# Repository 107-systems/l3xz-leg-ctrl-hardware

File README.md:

`l3xz-leg-ctrl-hardware`
========================

Custom leg controller board for the [L3X-Z Hexapod](https://github.com/107-systems/l3xz-hw).

<p align="center">
  
</p>

## Firmware
[l3xz-leg-ctrl-firmware](https://github.com/107-systems/l3xz-leg-ctrl-firmware)

## Pin Usage
### Arduino Nano 33 IoT connector CN1
| **Pin** | **Pin Name** | **Signal**    | **Description**                  |
|:-------:|:------------:|:-------------:|:--------------------------------:|
| 1       | D13/SCK      | SPI_SCK       | SPI for CAN and AS5048 encoder   |
| 2       | +3V3         | 3V3-rail      | supply voltage for board         |
| 3       | AREF         |               |                                  |
| 4       | DAC0/A0      |               |                                  |
| 5       | A1           | +BATT_MEAS    | measurement of input voltage     |
| 6       | A2           |               |                                  |
| 7       | A3           |               |                                  |
| 8       | A4/SDA       | I2C_SDA       | I2C for eeprom and qwiic         |
| 9       | A5/SCL       | I2C_SCL       | I2C for eeprom and qwiic         |
| 10      | A6           | LED3          | status LED 3                     |
| 11      | A7           | LED2          | status LED 2                     |
| 12      | VUSB/+5V0    |               |                                  |
| 13      | REC/RESET    | RESET         | Reset                            |
| 14      | GND          | GND           | GND                              |
| 15      | VIN          | power input   | power input for board            |
| 16      | D1/TX        | SERIAL_TX     | to connector CN3                 |
| 17      | D0/RX        | SERIAL_RX     | to connector CN3                 |
| 18      | RESET        | RESET         | Reset                            |
| 19      | GND          | GND           | GND                              |
| 20      | D2           | LED1          | status LED 1                     |
| 21      | D3           | MCP2515_CS    | chip select for CAN              |
| 22      | D4           | AS5048_1_CS   | chip select for AS5048 1         |
| 23      | D5           | AS5048_2_CS   | chip select for AS5048 2         |
| 24      | D6           | BUMPER        | input for bumper                 |
| 25      | D7           | SERVO1        | PWM output for servo 1           |
| 26      | D8           |               |                                  |
| 27      | D9           | MCP2515_INT   | CAN interrupt                    |
| 28      | D10          | SERVO2        | PWM output for servo 2           |
| 29      | D11/MOSI     | SPI_MOSI      | SPI for CAN and AS5048 encoder   |
| 30      | D12/MISO     | SPI_MISO      | SPI for CAN and AS5048 encoder   |

### Qwiic I2C connector CN2
JST SH 1mm 4-pin.

| **Pin** | **Signal**    |
|:-------:|:-------------:|
| 1       | GND           |
| 2       | VCC           |
| 3       | I2C_SDA       |
| 4       | I2C_SCL       |

### Serial connector CN3
JST SH 1mm 4-pin.

| **Pin** | **Signal**    |
|:-------:|:-------------:|
| 1       | GND           |
| 2       | VCC           |
| 3       | SERIAL_TX     |
| 4       | SERIAL_RX     |

### Dronecode CAN connector CN4 and CN5
JST GH 1.25mm 4-pin.

| **Pin** | **Signal**    |
|:-------:|:-------------:|
| 1       | CANVCC        |
| 2       | CANH          |
| 3       | CANL          |
| 4       | GND           |

### Power Input CN6
Würth WR-TBL 3.81mm 2-pin.

| **Pin** | **Signal**    |       **Description**        |
|:-------:|:-------------:|:----------------------------:|
| 1       | V-IN          | Directly to Arduino Nano VIN |
| 2       | GND           |                              |

Attention: V_IN is 5 to 21 V and is directly connected to VIN of the Arduino with a diode for reverse polarity protection.
It is also directly connected to +5V of the servo connector. So it should be limited to +6V if servos are used.

### Cervo connector CN7
2x3 pin-header 2.54 mm.

| **Pin** | **Signal**    | **Description**                  |
|:-------:|:-------------:|:--------------------------------:|
| 1+2     | servo-pwm     | 50 Hz pulse signal               |
| 3+4     | +5V           | directly connected to VIN        |
| 5+6     | GND           |                                  |

### Bumper Connector CN8
WAGO 733-362 2.5mm 2-pin.

| **Pin** | **Signal**    | **Description**                  |
|:-------:|:-------------:|:--------------------------------:|
| 1       | BUMPER        | 10k pull up to +3.3V             |
| 2       | GND           |                                  |

## BOM

| **Designator** | **Part Name**             | **Link**                  |
|:--------------:|:-------------------------:|:--------------------------------:|
| C1, C2, C3, C4, C5, C6, C9 | Capacitor 0603 100nF 25V  |           |
| C7, C8         | do not install            |           |
| C10, C11       | do not install            |           |
| CN1            | Arduino Nano              | https://www.reichelt.de/praez-buchsenleisten-2-54-mm-1x15-gerade-mpe-115-1-015-p187279.html |
| CN2, CN3       | JST SH SM04B-SRSS-TB      |                                  |
| CN4, CN5       | JST GH SM04B-GHS-TB       | https://www.voelkner.de/products/1102742/JST-Stiftgehaeuse-Platine-GH-Polzahl-Gesamt-4-Rastermass-1.25mm-SM04B-GHS-TB-LF-SN.html           |
| CN6            | Würth WR-TBL 691322310002 |                                  |
| CN7            | Pinheader 2.54 mm 2x3     | https://www.reichelt.de/stiftleisten-2-54-mm-2x03-gewinkelt-mpe-088-2-006-p119904.html      |
| CN8            | WAGO 733-362              | https://www.reichelt.de/print-stiftleiste-micro-rm-2-5-gewinkelt-2-pol--wago-733-362-p45863.html |
| D1             | LED 0603 green            | https://www.reichelt.de/led-smd-1608-0603-gruen-112-mcd-120--led-el-0603-gr1-p156254.html   |
| D2, D3         | MBR0530T1G                | https://www.reichelt.de/schottkydiode-30-v-0-5-a-sod-123-mbr0530t1g-ons-p219621.html        |
| D4             | LED 0603 yellow           | https://www.reichelt.de/led-smd-1608-0603-gelb-180-mcd-120--led-el-0603-ge-p156259.html     |
| D5             | LED 0603 red              | https://www.reichelt.de/led-smd-1608-0603-rot-180-mcd-120--led-el-0603-rt-p156256.html      |
| R1, R2, R3, R4, R6, R7, R8, R9, R10, R14 | Resistor 0603 10k         |           |
| R5, R15, R16   | Resistor 0603 3k3         |           |
| R11, 12        | do not install            |           |
| R13            | Resistor 0603 100k        |           |
| U1, U2         | AS5048A                   |           |
| U3             | 24LC64-I/SN               | https://www.reichelt.de/eeprom-seriell-64-kb-8-k-x-8-i2c-2-5--5-5-v-so-8-24lc64-i-sn-p40079.html |
| U4             | MCP2515-I/P DIP-18        | https://www.reichelt.de/can-controller-mit-spi-schnittstelle-dil-18-mcp-2515-i-p-p54514.html |
| U8 alternative | MCP2515-I/SO SO-18        | https://www.reichelt.de/can-controller-mit-spi-schnittstelle-2-7--5-5-v-so-18-mcp-2515-i-so-p54515.html |
| U9             | SN65HVD232D               |           |
| U9 alternative | SN65HVD230D               | https://www.reichelt.de/high-speed-can-transceiver-1-mbit-s-3-3-v-so-8-sn-65hvd230d-p58427.html |
| Y1             | Quartz 16 MHz 5x2.5mm     | https://www.reichelt.de/keramik-smd-quarz-3x5x1mm-16-0mhz-16-000000-mj-p85005.html          |

## PCB
### Top
<p align="center">
  </a>
</p>
### Bottom
<p align="center">
  </a>
</p>

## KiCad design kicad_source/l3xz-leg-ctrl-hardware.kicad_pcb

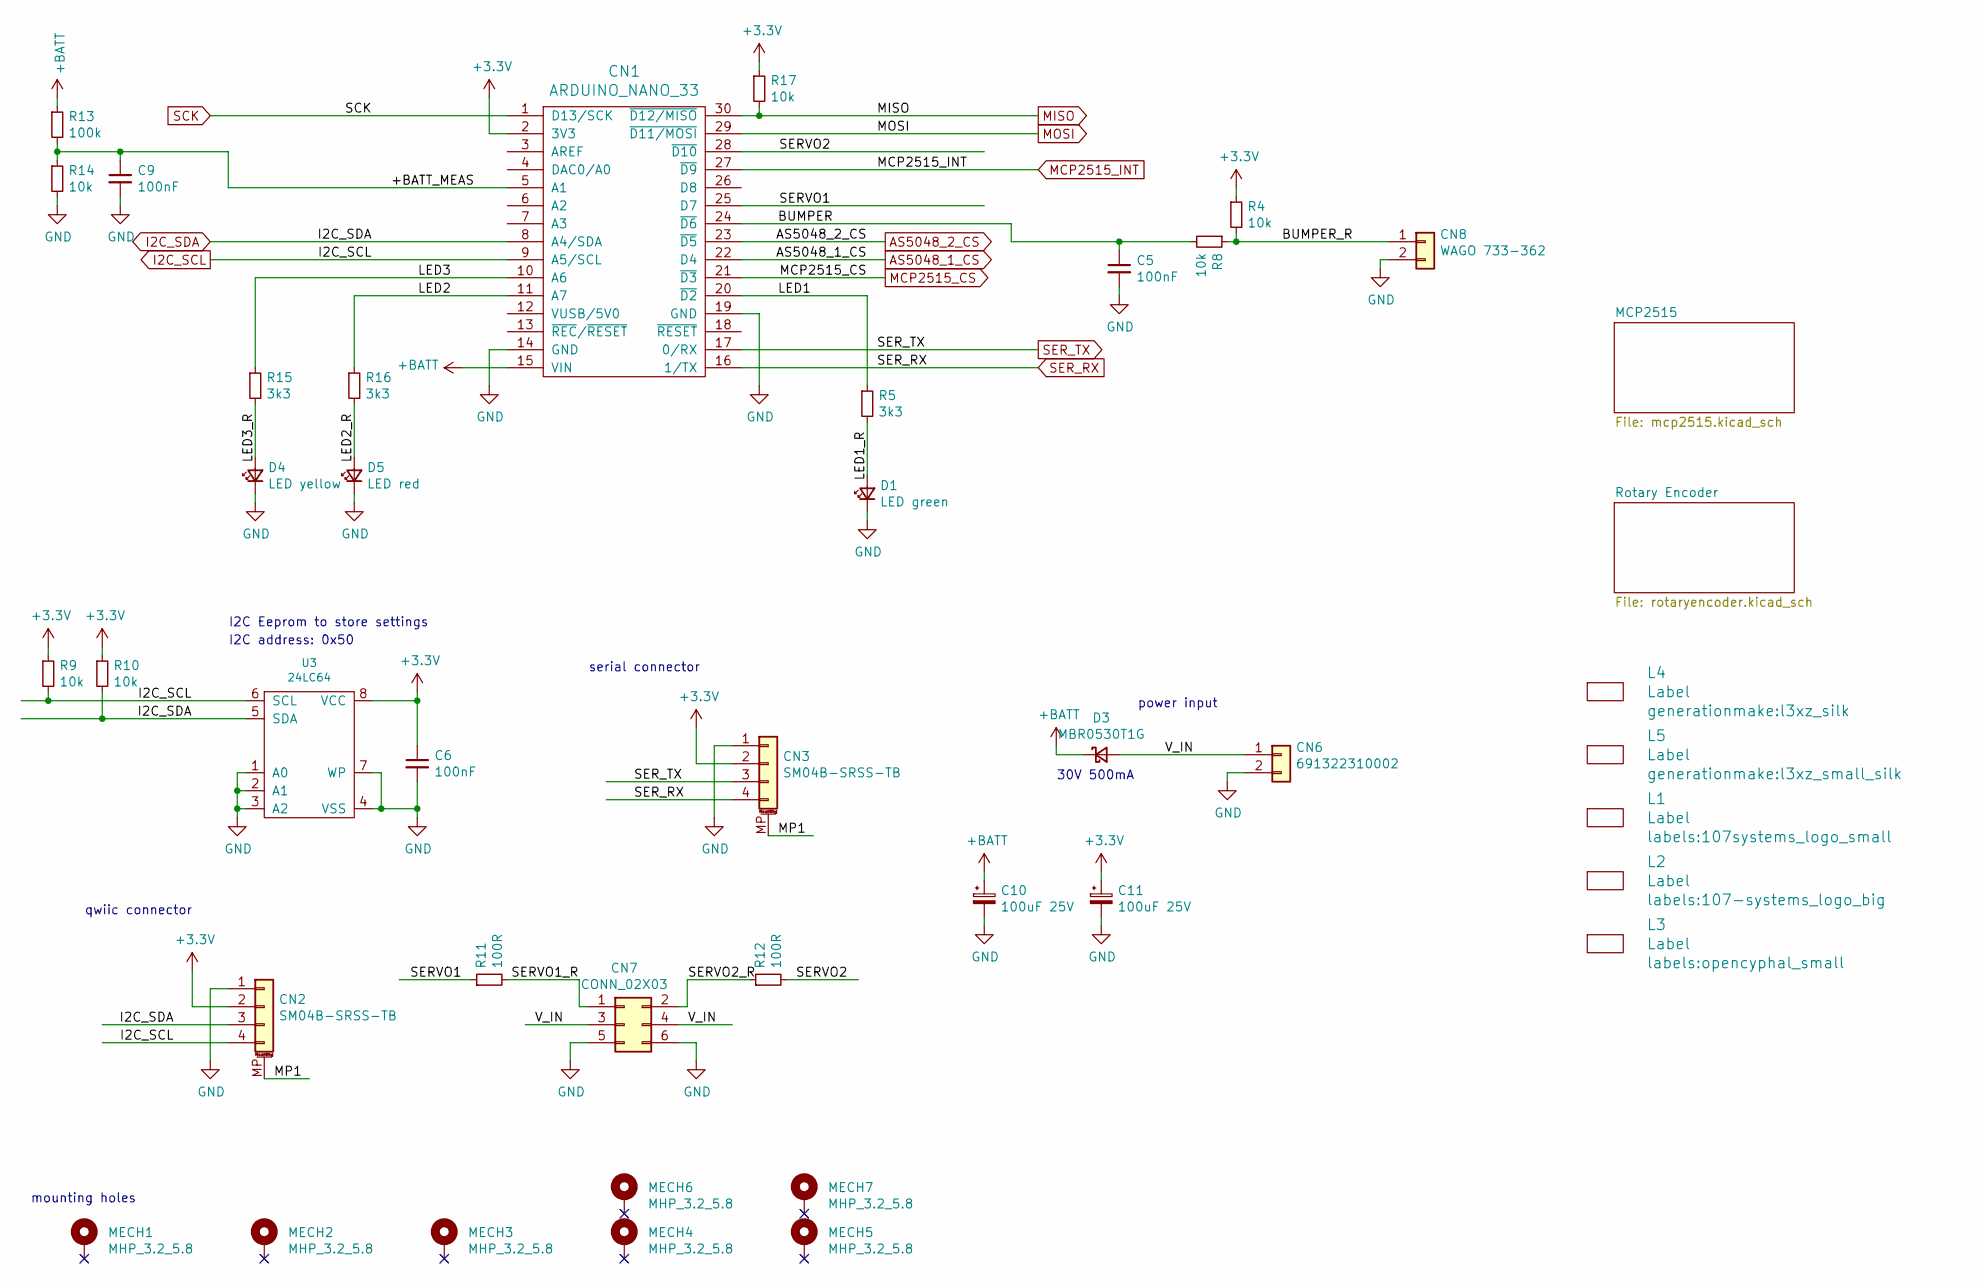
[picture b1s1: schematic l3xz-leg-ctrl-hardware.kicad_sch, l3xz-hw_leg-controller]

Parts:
C5, C6, C9: 100nF; C_0603_1608Metric
C10, C11: 100uF 25V; CP_Elec_8x10
CN1: ARDUINO_NANO_33
CN2, CN3: SM04B-SRSS-TB; JST_SH_SM04B-SRSS-TB_1x04-1MP_P1.00mm_Horizontal
CN6: 691322310002; WR-TBL_691322310002
CN7: CONN_02X03; PinHeader_2x03_P2.54mm_Horizontal
CN8: WAGO 733-362; WR-TBL_691382010002
D1: LED green; LED_0603
D3: MBR0530T1G; D_SOD-123
D4: LED yellow; LED_0603
D5: LED red; LED_0603
L1: Label; 107systems_logo_small
L2: Label; 107-systems_logo_big
L3: Label; opencyphal_small
L4: Label; l3xz_silk
L5: Label; l3xz_small_silk
MECH1, MECH2, MECH3, MECH4, MECH5, MECH6, MECH7: MHP_3.2_5.8
R4, R8, R9, R10, R14, R17: 10k; R_0603_1608Metric
R5, R15, R16: 3k3; R_0603_1608Metric
R11, R12: 100R; R_0603_1608Metric
R13: 100k; R_0603_1608Metric
U3: 24LC64; SOIC-8_3.9x4.9mm_P1.27mm

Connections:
+3.3V: C6.1, C11.1, CN1.2 (3V3), CN2.2, CN3.2, R4.1, R9.1, R10.1, R17.1, U3.8 (VCC); also elsewhere on the board
+BATT: C10.1, CN1.15 (VIN), D3.1 (K), R13.1; also elsewhere on the board
/+BATT_MEAS: C9.1, CN1.5 (A1), R13.2, R14.1
/BUMPER: C5.1, CN1.24 (~D6), R8.2
/BUMPER_R: CN8.1, R4.2, R8.1
/LED1: CN1.20 (~D2), R5.1
/LED1_R: D1.2 (A), R5.2
/LED2: CN1.11 (A7), R16.1
/LED2_R: D5.2 (A), R16.2
/LED3: CN1.10 (A6), R15.1
/LED3_R: D4.2 (A), R15.2
/MP1: CN2.MP (MountPin), CN3.MP (MountPin)
/SERVO1: CN1.25 (D7), R11.1
/SERVO1_R: CN7.1, R11.2
/SERVO2: CN1.28 (~D10), R12.2
/SERVO2_R: CN7.2, R12.1
/V_IN: CN6.1, CN7.3, CN7.4, D3.2 (A)
AS5048_1_CS: CN1.22 (D4); also elsewhere on the board
AS5048_2_CS: CN1.23 (~D5); also elsewhere on the board
GND: C5.2, C6.2, C9.2, C10.2, C11.2, CN1.14 (GND), CN1.19 (GND), CN2.1, CN3.1, CN6.2, CN7.5, CN7.6, CN8.2, D1.1 (K), D4.1 (K), D5.1 (K), R14.2, U3.1 (A0), U3.2 (A1), U3.3 (A2), U3.4 (VSS), U3.7 (WP); also elsewhere on the board
I2C_SCL: CN1.9 (A5/SCL), CN2.4, R9.2, U3.6 (SCL)
I2C_SDA: CN1.8 (A4/SDA), CN2.3, R10.2, U3.5 (SDA)
MCP2515_CS: CN1.21 (~D3); also elsewhere on the board
MCP2515_INT: CN1.27 (~D9); also elsewhere on the board
MISO: CN1.30 (~D12/MISO), R17.2; also elsewhere on the board
MOSI: CN1.29 (~D11/MOSI); also elsewhere on the board
SCK: CN1.1 (D13/SCK); also elsewhere on the board
SER_RX: CN1.16 (1/TX), CN3.4
SER_TX: CN1.17 (0/RX), CN3.3

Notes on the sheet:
serial connector
power input
I2C address: 0x50
qwiic connector
mounting holes
30V 500mA
I2C Eeprom to store settings

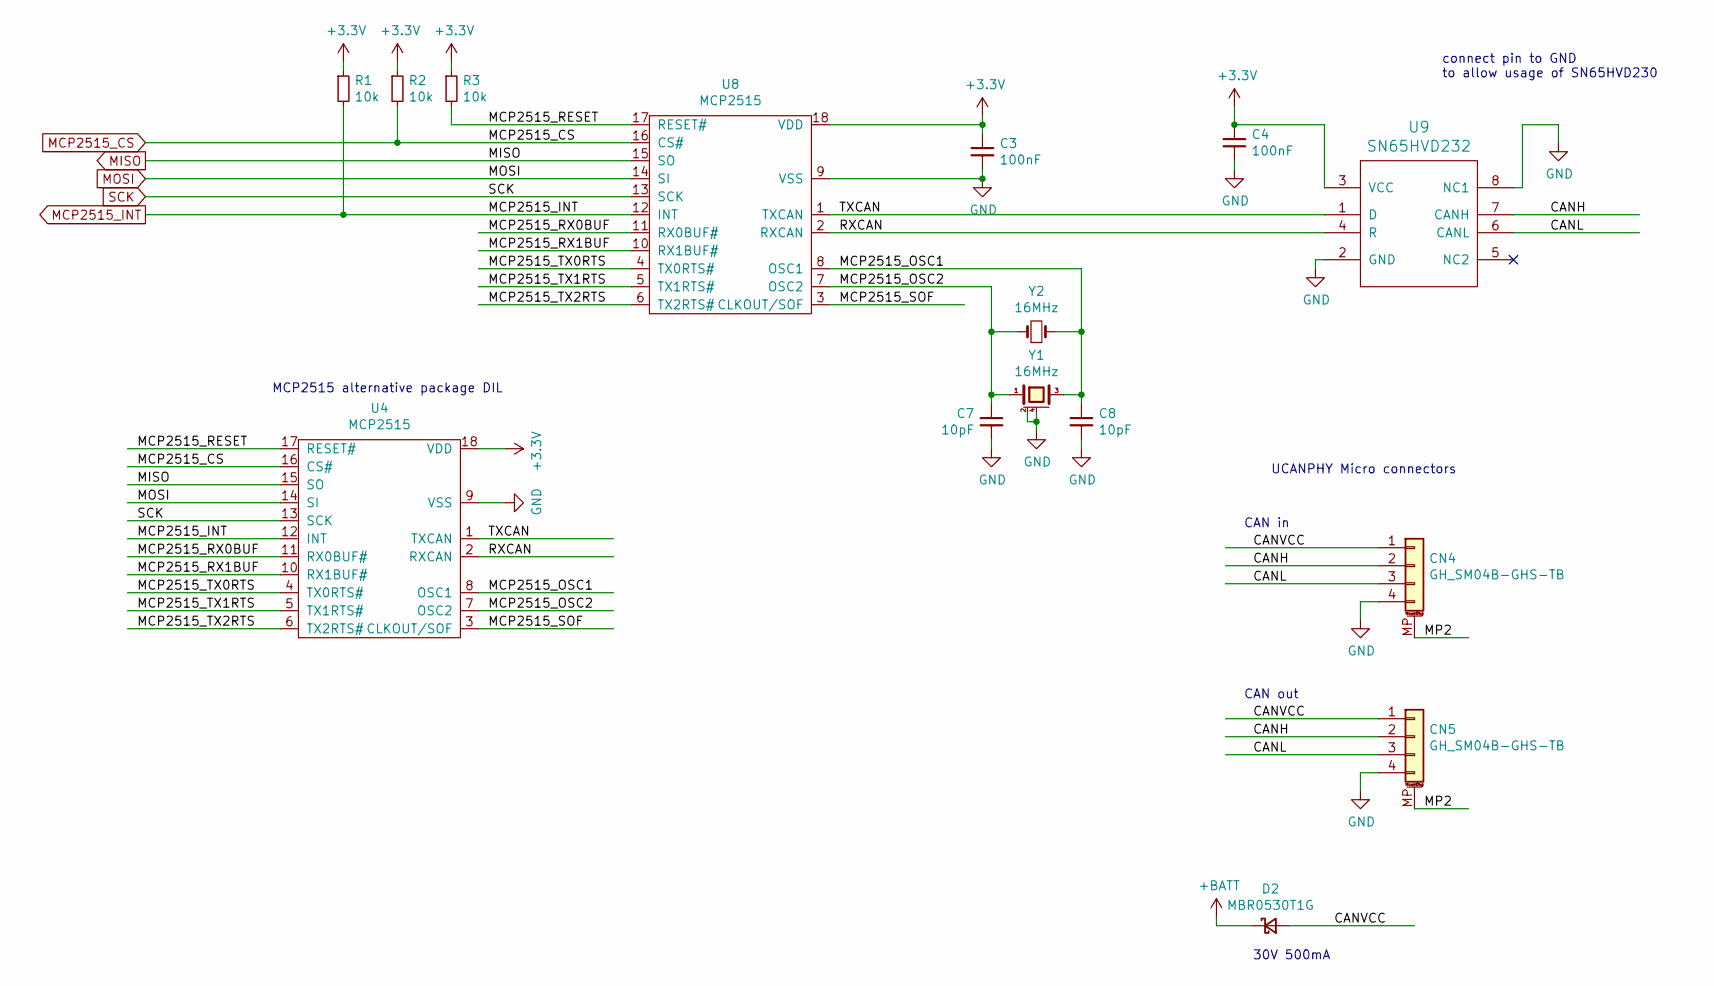
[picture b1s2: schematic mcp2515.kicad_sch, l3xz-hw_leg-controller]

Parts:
C3, C4: 100nF; C_0603_1608Metric
C7, C8: 10pF; C_0603_1608Metric
CN4, CN5: GH_SM04B-GHS-TB; JST_GH_SM04B-GHS-TB_1x04-1MP_P1.25mm_Horizontal
D2: MBR0530T1G; D_SOD-123
R1, R2, R3: 10k; R_0603_1608Metric
U4: MCP2515; DIP-18_W7.62mm
U8: MCP2515; SOIC-18W_7.5x11.6mm_P1.27mm
U9: SN65HVD232; SOIC-8_3.9x4.9mm_P1.27mm
Y1: 16MHz; Crystal_SMD_SeikoEpson_FA238V-4Pin_3.2x2.5mm
Y2: 16MHz; Crystal_HC49-U_Vertical

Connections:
+3.3V: C3.1, C4.1, R1.1, R2.1, R3.1, U4.18 (VDD), U8.18 (VDD), U9.3 (VCC); also elsewhere on the board
+BATT: D2.1 (K); also elsewhere on the board
/MCP2515/CANH: CN4.2, CN5.2, U9.7 (CANH)
/MCP2515/CANL: CN4.3, CN5.3, U9.6 (CANL)
/MCP2515/CANVCC: CN4.1, CN5.1, D2.2 (A)
/MCP2515/MCP2515_OSC1: C8.1, U4.8 (OSC1), U8.8 (OSC1), Y1.3, Y2.2
/MCP2515/MCP2515_OSC2: C7.1, U4.7 (OSC2), U8.7 (OSC2), Y1.1, Y2.1
/MCP2515/MCP2515_RESET: R3.2, U4.17 (RESET#), U8.17 (RESET#)
/MCP2515/MCP2515_RX0BUF: U4.11 (RX0BUF#), U8.11 (RX0BUF#)
/MCP2515/MCP2515_RX1BUF: U4.10 (RX1BUF#), U8.10 (RX1BUF#)
/MCP2515/MCP2515_SOF: U4.3 (CLKOUT/SOF), U8.3 (CLKOUT/SOF)
/MCP2515/MCP2515_TX0RTS: U4.4 (TX0RTS#), U8.4 (TX0RTS#)
/MCP2515/MCP2515_TX1RTS: U4.5 (TX1RTS#), U8.5 (TX1RTS#)
/MCP2515/MCP2515_TX2RTS: U4.6 (TX2RTS#), U8.6 (TX2RTS#)
/MCP2515/MP2: CN4.MP (MountPin), CN5.MP (MountPin)
/MCP2515/RXCAN: U4.2 (RXCAN), U8.2 (RXCAN), U9.4 (R)
/MCP2515/TXCAN: U4.1 (TXCAN), U8.1 (TXCAN), U9.1 (D)
GND: C3.2, C4.2, C7.2, C8.2, CN4.4, CN5.4, U4.9 (VSS), U8.9 (VSS), U9.2 (GND), U9.8 (NC1), Y1.2 (case), Y1.4 (case); also elsewhere on the board
MCP2515_CS: R2.2, U4.16 (CS#), U8.16 (CS#); also elsewhere on the board
MCP2515_INT: R1.2, U4.12 (INT), U8.12 (INT); also elsewhere on the board
MISO: U4.15 (SO), U8.15 (SO); also elsewhere on the board
MOSI: U4.14 (SI), U8.14 (SI); also elsewhere on the board
SCK: U4.13 (SCK), U8.13 (SCK); also elsewhere on the board

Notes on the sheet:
connect pin to GND to allow usage of SN65HVD230
CAN out
UCANPHY Micro connectors
CAN in
MCP2515 alternative package DIL
30V 500mA

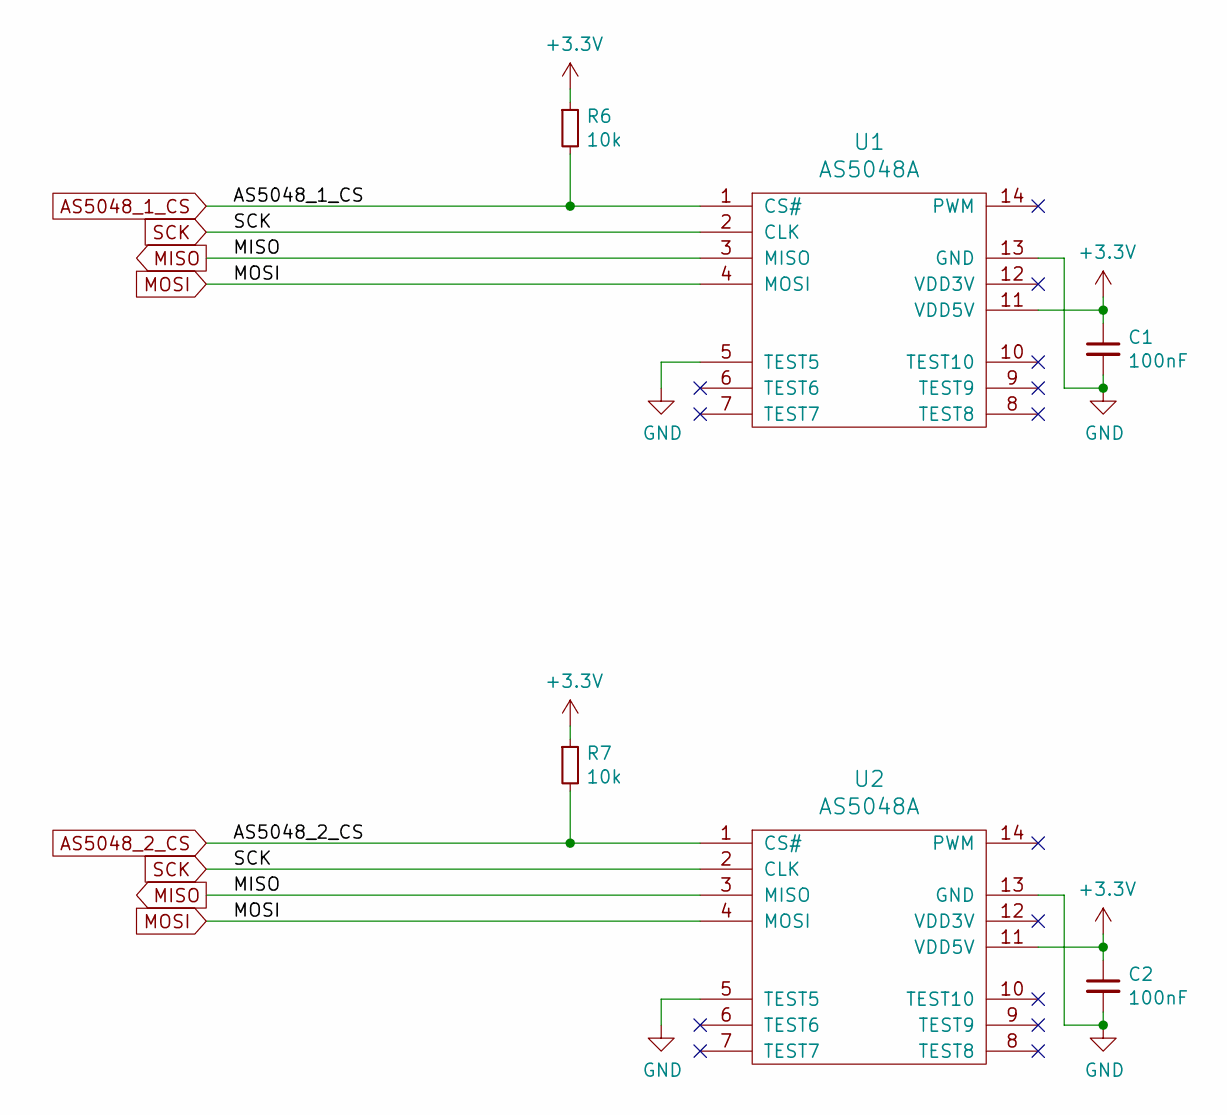
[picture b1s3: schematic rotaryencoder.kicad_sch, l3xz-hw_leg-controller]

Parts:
C1, C2: 100nF; C_0603_1608Metric
R6, R7: 10k; R_0603_1608Metric
U1, U2: AS5048A; TSSOP-14_4.4x5mm_P0.65mm

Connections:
+3.3V: C1.1, C2.1, R6.1, R7.1, U1.11 (VDD5V), U2.11 (VDD5V); also elsewhere on the board
AS5048_1_CS: R6.2, U1.1 (CS#); also elsewhere on the board
AS5048_2_CS: R7.2, U2.1 (CS#); also elsewhere on the board
GND: C1.2, C2.2, U1.5 (TEST5), U1.13 (GND), U2.5 (TEST5), U2.13 (GND); also elsewhere on the board
MISO: U1.3 (MISO), U2.3 (MISO); also elsewhere on the board
MOSI: U1.4 (MOSI), U2.4 (MOSI); also elsewhere on the board
SCK: U1.2 (CLK), U2.2 (CLK); also elsewhere on the board

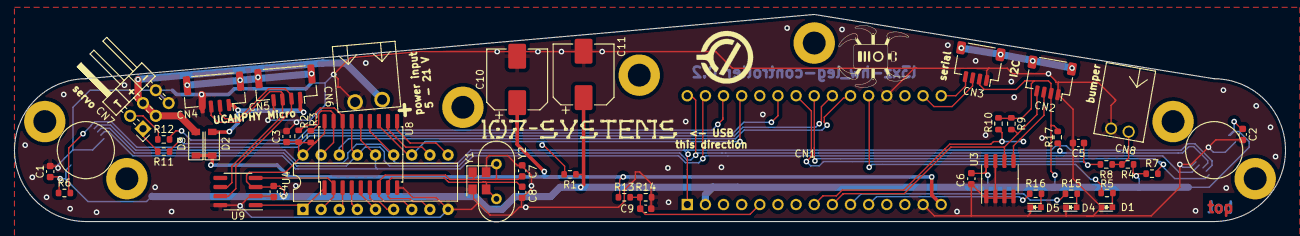
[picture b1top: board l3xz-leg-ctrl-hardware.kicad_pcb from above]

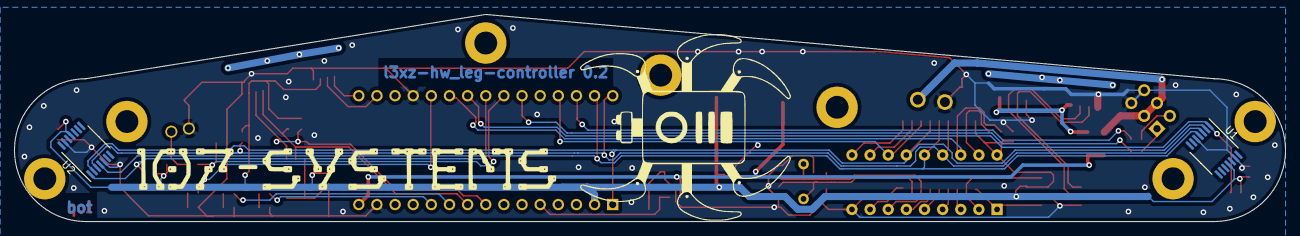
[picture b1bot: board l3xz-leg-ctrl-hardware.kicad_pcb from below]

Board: 2 copper layers, 178.0 x 29.0 mm, 61 parts (4 on the bottom side), 44 nets.

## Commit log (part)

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2022-04-03 added first draft of pcb
2022-04-03 added step file
2022-04-03 updated spec
2022-04-03 added rotary encoder, led and switch
2022-04-03 added schematic pdf
2022-04-04 added images
2022-04-07 added dronecode can and qwiic connectors
2022-04-07 added eeprom and servo connectors, updated pdf
2022-04-08 updated schematic, corrected connector designators, updated footprints
2022-04-08 made first draft for layout
2022-04-08 added pull up to i2c, serial resistor to servo
2022-04-10 updated connectors, added power input
2022-04-10 added additional leds, input measurement buffer capacitors
2022-04-10 added labels, beautified layout
2022-04-10 updated schematic pdf and images
2022-04-17 updated step model, added link to software in readme
2022-05-03 added BOM to readme
2022-05-08 updated some part values
2022-05-29 updated BOM in readme and schematic, updated schematic pdf
2022-05-29 exchanged pin D7 and D9 and connected U9, pin8 to GND in readme and schematic as all boards have been reworked
2022-06-05 fixed MCP2515_INT and direction label for Arduino
2022-06-05 fixed crystal issues, corrected CAN driver footprint, added pullup on MISO
2022-06-05 updated images and schematic pdf
2022-06-08 Adding sync-labels workflow.
2022-06-08 Adding sync-labels workflow. (#9)
2022-08-23 Add l3xz logo.
2022-08-23 Add l3xz logo. (#10)
2022-08-24 Increase logo size to 40%.
2022-10-17 enroll dependabot
2022-10-17 Bump geekyeggo/delete-artifact from 1 to 2
    Bumps [geekyeggo/delete-artifact](https://github.com/geekyeggo/delete-artifact) from 1 to 2.
    - [Release notes](https://github.com/geekyeggo/delete-artifact/releases)
    - [Commits](https://github.com/geekyeggo/delete-artifact/compare/v1...v2)
    ---
    updated-dependencies:
    - dependency-name: geekyeggo/delete-artifact
2022-10-17 Bump actions/checkout from 2 to 3
    Bumps [actions/checkout](https://github.com/actions/checkout) from 2 to 3.
    - [Release notes](https://github.com/actions/checkout/releases)
    - [Changelog](https://github.com/actions/checkout/blob/main/CHANGELOG.md)
    - [Commits](https://github.com/actions/checkout/compare/v2...v3)
    ---
    updated-dependencies:
2022-10-17 Bump actions/upload-artifact from 2 to 3
    Bumps [actions/upload-artifact](https://github.com/actions/upload-artifact) from 2 to 3.
    - [Release notes](https://github.com/actions/upload-artifact/releases)
    - [Commits](https://github.com/actions/upload-artifact/compare/v2...v3)
    ---
    updated-dependencies:
    - dependency-name: actions/upload-artifact
2022-10-17 Bump carlosperate/download-file-action from 1.0.3 to 1.1.1
    Bumps [carlosperate/download-file-action](https://github.com/carlosperate/download-file-action) from 1.0.3 to 1.1.1.
    - [Release notes](https://github.com/carlosperate/download-file-action/releases)
    - [Commits](https://github.com/carlosperate/download-file-action/compare/v1.0.3...v1.1.1)
    ---
    updated-dependencies:
    - dependency-name: carlosperate/download-file-action
2022-10-17 Bump actions/download-artifact from 2 to 3
    Bumps [actions/download-artifact](https://github.com/actions/download-artifact) from 2 to 3.
    - [Release notes](https://github.com/actions/download-artifact/releases)
    - [Commits](https://github.com/actions/download-artifact/compare/v2...v3)
    ---
    updated-dependencies:
    - dependency-name: actions/download-artifact
2022-10-17 Bump actions/download-artifact from 2 to 3 (#16)
    Bumps [actions/download-artifact](https://github.com/actions/download-artifact) from 2 to 3.
    - [Release notes](https://github.com/actions/download-artifact/releases)
    - [Commits](https://github.com/actions/download-artifact/compare/v2...v3)
    ---
    updated-dependencies:
    - dependency-name: actions/download-artifact
2022-10-17 Bump carlosperate/download-file-action from 1.0.3 to 1.1.1 (#15)
    Bumps [carlosperate/download-file-action](https://github.com/carlosperate/download-file-action) from 1.0.3 to 1.1.1.
    - [Release notes](https://github.com/carlosperate/download-file-action/releases)
    - [Commits](https://github.com/carlosperate/download-file-action/compare/v1.0.3...v1.1.1)
    ---
    updated-dependencies:
    - dependency-name: carlosperate/download-file-action
2022-10-17 Bump actions/upload-artifact from 2 to 3 (#14)
    Bumps [actions/upload-artifact](https://github.com/actions/upload-artifact) from 2 to 3.
    - [Release notes](https://github.com/actions/upload-artifact/releases)
    - [Commits](https://github.com/actions/upload-artifact/compare/v2...v3)
    ---
    updated-dependencies:
    - dependency-name: actions/upload-artifact
2022-10-17 Bump actions/checkout from 2 to 3 (#13)
    Bumps [actions/checkout](https://github.com/actions/checkout) from 2 to 3.
    - [Release notes](https://github.com/actions/checkout/releases)
    - [Changelog](https://github.com/actions/checkout/blob/main/CHANGELOG.md)
    - [Commits](https://github.com/actions/checkout/compare/v2...v3)
    ---
    updated-dependencies:
2022-10-17 Bump geekyeggo/delete-artifact from 1 to 2 (#12)
    Bumps [geekyeggo/delete-artifact](https://github.com/geekyeggo/delete-artifact) from 1 to 2.
    - [Release notes](https://github.com/geekyeggo/delete-artifact/releases)
    - [Commits](https://github.com/geekyeggo/delete-artifact/compare/v1...v2)
    ---
    updated-dependencies:
    - dependency-name: geekyeggo/delete-artifact
2022-10-24 Bump carlosperate/download-file-action from 1.1.1 to 2.0.0
    Bumps [carlosperate/download-file-action](https://github.com/carlosperate/download-file-action) from 1.1.1 to 2.0.0.
    - [Release notes](https://github.com/carlosperate/download-file-action/releases)
    - [Commits](https://github.com/carlosperate/download-file-action/compare/v1.1.1...v2.0.0)
    ---
    updated-dependencies:
    - dependency-name: carlosperate/download-file-action
2022-10-24 Bump carlosperate/download-file-action from 1.1.1 to 2.0.0 (#17)
    Bumps [carlosperate/download-file-action](https://github.com/carlosperate/download-file-action) from 1.1.1 to 2.0.0.
    - [Release notes](https://github.com/carlosperate/download-file-action/releases)
    - [Commits](https://github.com/carlosperate/download-file-action/compare/v1.1.1...v2.0.0)
    ---
    updated-dependencies:
    - dependency-name: carlosperate/download-file-action
2023-01-25 Rename repository to l3xz-leg-ctrl-hardware.
2023-01-25 Rename repository to l3xz-leg-ctrl-hardware. (#18)
2023-01-25 Pretty up README.
2023-01-25 updated project to kicad 6
2023-01-25 updated some symbol library links
2023-01-26 Fix position/size of logol
2023-01-29 updated footprint library
2023-01-29 connected mounting pads of connectors
2023-01-30 fixed drc errors
2023-01-30 added labels, updated pdf schematic and images
2023-01-30 updated step file
2023-02-20 License under CERN Open Hardware Licence Version 2.
2023-02-20 License under CERN Open Hardware Licence Version 2. (#22)
2023-02-20 Add CI workflow to check for commonly misspelled words
    On every push, pull request, and periodically, use codespell to check for commonly
    misspelled words.
    In the event of a false positive, the problematic word should be added, in all lowercase, to the
    field of . Regardless of the case of the word in the false positive, it must be in all lowercase in the
    ignore list. The ignore list is comma-separated with no spaces.
2023-02-20 Add CI workflow to check for commonly misspelled words (#23)
    On every push, pull request, and periodically, use codespell to check for commonly
    misspelled words.
    In the event of a false positive, the problematic word should be added, in all lowercase, to the
    field of . Regardless of the case of the word in the false positive, it must be in all lowercase in the
    ignore list. The ignore list is comma-separated with no spaces.
2023-08-09 Bump carlosperate/download-file-action from 2.0.0 to 2.0.1
    Bumps [carlosperate/download-file-action](https://github.com/carlosperate/download-file-action) from 2.0.0 to 2.0.1.
    - [Release notes](https://github.com/carlosperate/download-file-action/releases)
    - [Commits](https://github.com/carlosperate/download-file-action/compare/v2.0.0...v2.0.1)
    ---
    updated-dependencies:
    - dependency-name: carlosperate/download-file-action
2023-08-09 Bump carlosperate/download-file-action from 2.0.0 to 2.0.1 (#25)
    Bumps [carlosperate/download-file-action](https://github.com/carlosperate/download-file-action) from 2.0.0 to 2.0.1.
    - [Release notes](https://github.com/carlosperate/download-file-action/releases)
    - [Commits](https://github.com/carlosperate/download-file-action/compare/v2.0.0...v2.0.1)
    ---
    updated-dependencies:
    - dependency-name: carlosperate/download-file-action
2023-09-05 Bump actions/checkout from 3 to 4 (#26)
    Bumps [actions/checkout](https://github.com/actions/checkout) from 3 to 4.
    - [Release notes](https://github.com/actions/checkout/releases)
    - [Changelog](https://github.com/actions/checkout/blob/main/CHANGELOG.md)
    - [Commits](https://github.com/actions/checkout/compare/v3...v4)
    ---
    updated-dependencies:
2023-12-15 Bump actions/upload-artifact from 3 to 4
    Bumps [actions/upload-artifact](https://github.com/actions/upload-artifact) from 3 to 4.
    - [Release notes](https://github.com/actions/upload-artifact/releases)
    - [Commits](https://github.com/actions/upload-artifact/compare/v3...v4)
    ---
    updated-dependencies:
    - dependency-name: actions/upload-artifact
2023-12-15 Bump actions/download-artifact from 3 to 4
    Bumps [actions/download-artifact](https://github.com/actions/download-artifact) from 3 to 4.
    - [Release notes](https://github.com/actions/download-artifact/releases)
    - [Commits](https://github.com/actions/download-artifact/compare/v3...v4)
    ---
    updated-dependencies:
    - dependency-name: actions/download-artifact
2023-12-15 Bump actions/download-artifact from 3 to 4 (#30)
    Bumps [actions/download-artifact](https://github.com/actions/download-artifact) from 3 to 4.
    - [Release notes](https://github.com/actions/download-artifact/releases)
    - [Commits](https://github.com/actions/download-artifact/compare/v3...v4)
    ---
    updated-dependencies:
    - dependency-name: actions/download-artifact
2023-12-15 Bump actions/upload-artifact from 3 to 4 (#29)
    Bumps [actions/upload-artifact](https://github.com/actions/upload-artifact) from 3 to 4.
    - [Release notes](https://github.com/actions/upload-artifact/releases)
    - [Commits](https://github.com/actions/upload-artifact/compare/v3...v4)
    ---
    updated-dependencies:
    - dependency-name: actions/upload-artifact
2023-12-25 Bump geekyeggo/delete-artifact from 2 to 4
    Bumps [geekyeggo/delete-artifact](https://github.com/geekyeggo/delete-artifact) from 2 to 4.
    - [Release notes](https://github.com/geekyeggo/delete-artifact/releases)
    - [Changelog](https://github.com/GeekyEggo/delete-artifact/blob/main/CHANGELOG.md)
    - [Commits](https://github.com/geekyeggo/delete-artifact/compare/v2...v4)
    ---
    updated-dependencies:
2023-12-25 Bump geekyeggo/delete-artifact from 2 to 4 (#31)
    Bumps [geekyeggo/delete-artifact](https://github.com/geekyeggo/delete-artifact) from 2 to 4.
    - [Release notes](https://github.com/geekyeggo/delete-artifact/releases)
    - [Changelog](https://github.com/GeekyEggo/delete-artifact/blob/main/CHANGELOG.md)
    - [Commits](https://github.com/geekyeggo/delete-artifact/compare/v2...v4)
    ---
    updated-dependencies:
2024-03-19 Bump geekyeggo/delete-artifact from 4 to 5
    Bumps [geekyeggo/delete-artifact](https://github.com/geekyeggo/delete-artifact) from 4 to 5.
    - [Release notes](https://github.com/geekyeggo/delete-artifact/releases)
    - [Changelog](https://github.com/GeekyEggo/delete-artifact/blob/main/CHANGELOG.md)
    - [Commits](https://github.com/geekyeggo/delete-artifact/compare/v4...v5)
    ---
    updated-dependencies:
